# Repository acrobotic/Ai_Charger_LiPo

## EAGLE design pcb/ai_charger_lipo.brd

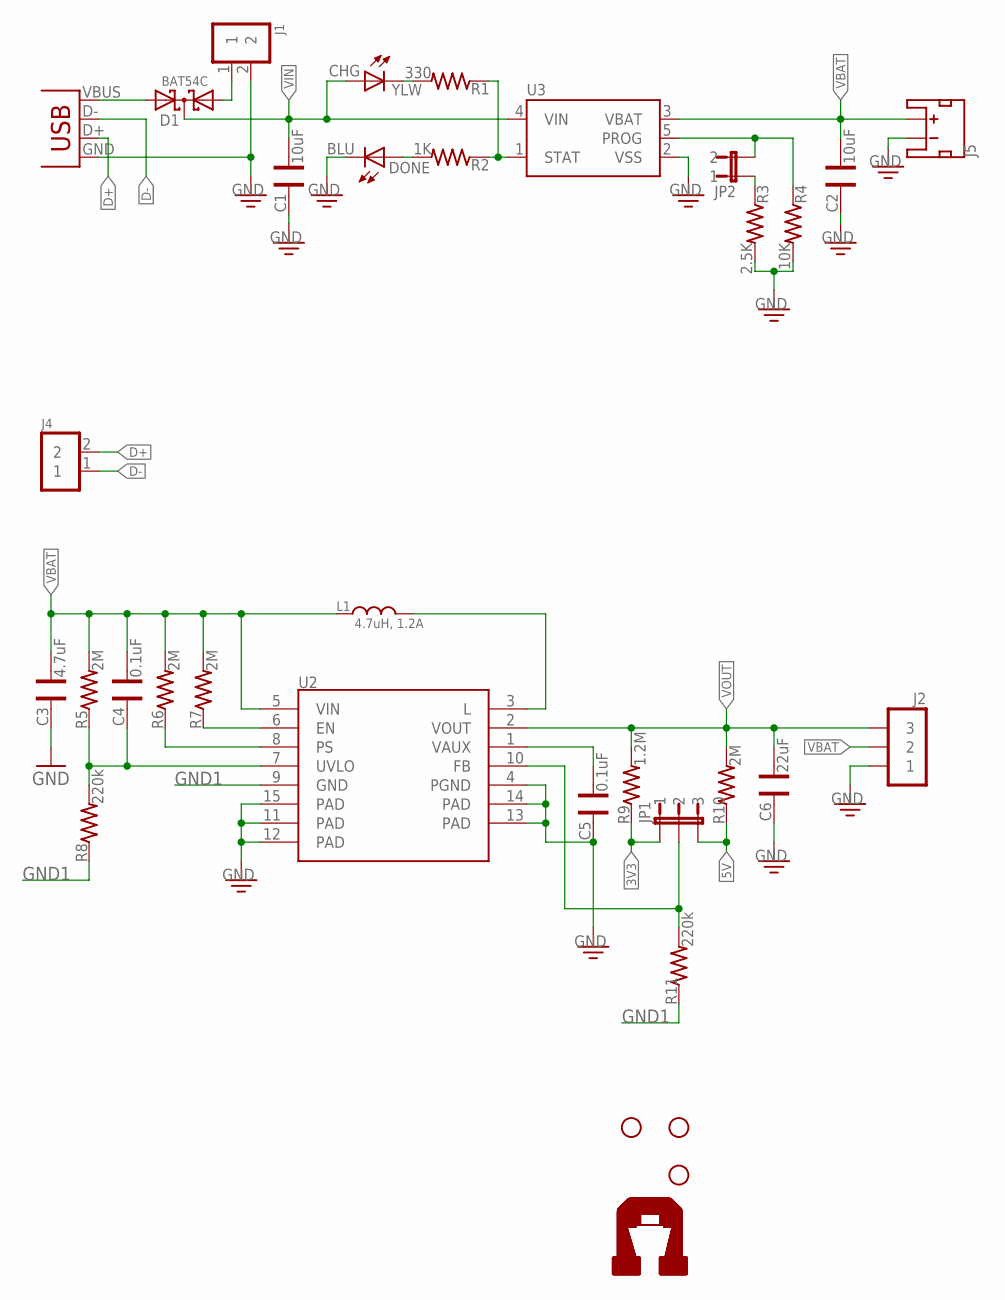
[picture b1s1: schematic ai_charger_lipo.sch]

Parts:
C1, C2: 10uF; CAP-0603
C3: 4.7uF; CAP-0603
C4, C5: 0.1uF; CAP-0603
C6: 22uF; CAP-0603
CHG: YLW; LED-0603
D1: BAT54C; SOT-23
DONE: BLU; LED-0603
J1: 1X02ST; 1X02-ST
J2: 1X03NOFIRST; 1X03-NOFIRST
J4: 1X02NOFIRST; 1X02-NOFIRST
J5: JST-2-MALE; JST-2-SMD
JP1: 1X03-PJNOFIRST; 1X03-NOFIRST
JP2: 1X02-PJNOFIRST; 1X02-NOFIRST
L1: 4.7uH, 1.2A; IND-0603
R1: 330; RES-0603
R2: 1K; RES-0603
R3: 2.5K; RES-0603
R4: 10K; RES-0603
R5, R6, R7, R10: 2M; RES-0603
R8, R11: 220k; RES-0603
R9: 1.2M; RES-0603
STANDOFF1, STANDOFF2, STANDOFF3: STAND-OFF
U2: TPS61200; QFN-10-PAD
U3: MCP73831; SOT23-5
U$1, U$2: AI-LOGOXS; AI-LOGO-XS
X2: USBMICROB-TH; USB-MICROB-TH

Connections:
3V3: JP1.1, R9.1
5V: JP1.3, R10.1
D+: J4.2, X2.D+
D-: J4.1, X2.D-
EN: R7.1, U2.6 (EN)
FB: JP1.2, R11.2, U2.10 (FB)
GND: C1.2, C2.2, C3.2, C5.2, C6.2, DONE.C, J1.2, J2.1, J5.2 (-), R3.2, R4.2, U2.4 (PGND), U2.11 (PAD), U2.12 (PAD), U2.13 (PAD), U2.14 (PAD), U2.15 (PAD), U3.2 (VSS), X2.GND
GND1: R8.1, R11.1, U2.9 (GND)
unnamed: C5.1, U2.1 (VAUX)
unnamed: L1.1, U2.3 (L)
unnamed: JP2.2, R4.1, U3.5 (PROG)
unnamed: R1.1, R2.1, U3.1 (STAT)
unnamed: CHG.C, R1.2
unnamed: D1.1 (A1), J1.1
unnamed: D1.2 (A2), X2.VBUS
unnamed: DONE.A, R2.2
unnamed: JP2.1, R3.1
PS: R6.1, U2.8 (PS)
UVLO: C4.2, R5.1, R8.2, U2.7 (UVLO)
VBAT: C2.1, C3.1, C4.1, J2.2, J5.1 (+), L1.2, R5.2, R6.2, R7.2, U2.5 (VIN), U3.3 (VBAT)
VIN: C1.1, CHG.A, D1.3 (CC), U3.4 (VIN)
VOUT: C6.1, J2.3, R9.2, R10.2, U2.2 (VOUT)

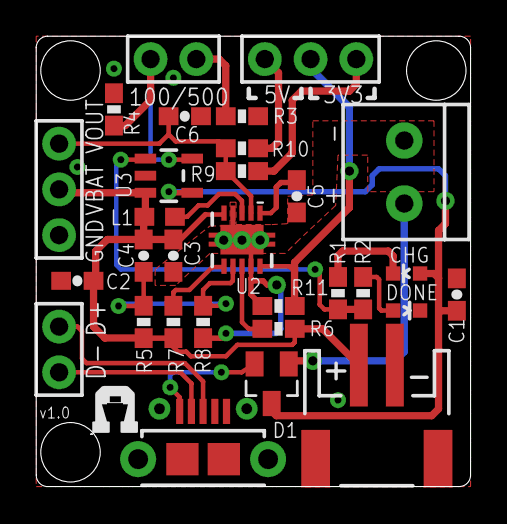
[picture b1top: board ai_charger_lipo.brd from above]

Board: 2 copper layers, 24.1 x 25.0 mm, 35 parts (1 on the bottom side), 22 nets.

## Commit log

2014-10-20 done fab
